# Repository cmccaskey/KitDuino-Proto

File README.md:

# About #
Thunkit Electronics sells electronic kits and rocket altimeters, available at [thunkitelectronics.com](https://thunkitelectronics.com) and [Tindie](https://www.tindie.com/stores/cmccaskey). All designs are open source with schematics, board layouts, code, and BOMs available. The Creative Commons Attribution-NonCommercial-ShareAlike 4.0 International License is used and can be read [here]( https://creativecommons.org/licenses/by-nc-sa/4.0/legalcode).

## Description ###
 <br />
The KitDuino Proto is a 32u4 Arduino compatible with built in prototyping area. The board supports 3 voltage modes selectable by jumpers: 3.3V regulated, 5V regulated, and Vin direct with no regulation.

## Why KitDuino Proto? ## 
The KitDuino Proto is a one of a kind Arduino compatible board. It uses the Atmel ATmega32u4 and can be programmed by the Arduino IDE using the Thunkit Arduino Core available [here](https://github.com/cmccaskey/Thunkit-Arduino-Core/tree/master).The KitDuino Proto has a small prototyping area making it a great addition to your next project.

## Technical Specifications ##
The KitDuino Proto runs at 8MHz to allow for 3.3V and 5V operation. The KitDuino Proto supports 3 voltage modes. By default, the board will run at 3.3V. By installing the jumper in the '5V SEL' position, the board will run at 5V. When powered over USB, due to losses in the regulator circuit, the board will run at approximately 3.8V. If an external voltage sorce of 7V or higher is used, a stable 5V rail will be generated by the regulator. For projects that are always powered off of USB and never see a Vin of more than 5V, the 'Vin SEL' jumper can be installed. This jumper directly connects the USB voltage (after schottky diode) to VCC. Beware! Installing the 'Vin SEL' jumper and connecting a Vin of more than 5V can cause permanent damage to your board!

## BOM ##
KiCad interactive BOM available at [thunkitelectronics.com](https://thunkitelectronics.com).

## Schematic ##
 <br />

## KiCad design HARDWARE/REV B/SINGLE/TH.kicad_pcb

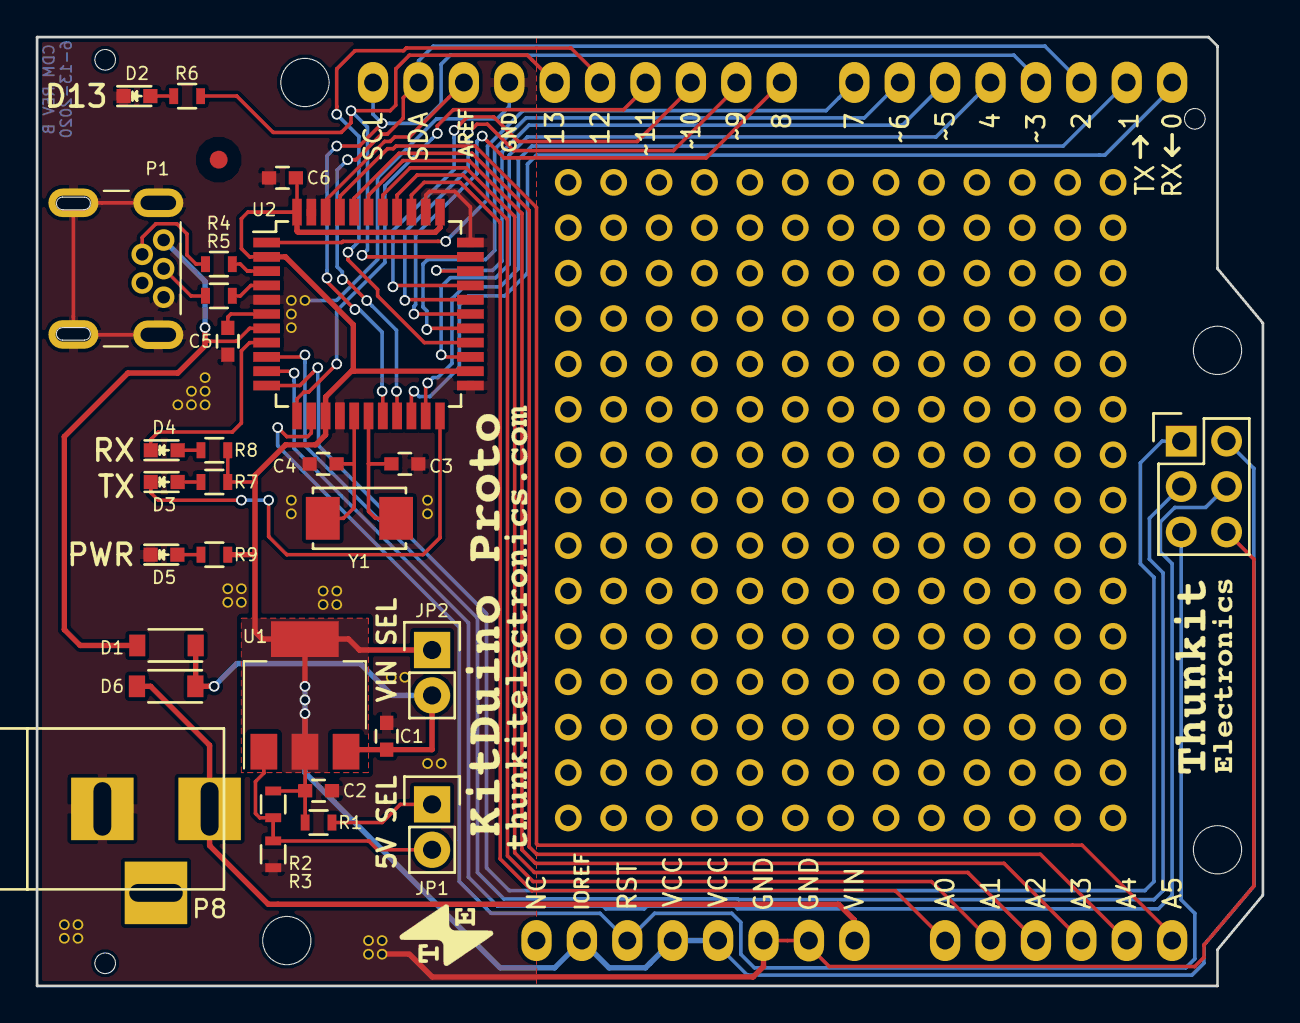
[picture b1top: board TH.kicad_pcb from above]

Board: 2 copper layers, 68.6 x 53.1 mm, 33 parts (0 on the bottom side), 45 nets.

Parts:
C1, C2, C5, C6: 1uF; C_0603
C3, C4: 22pF; C_0603
D1, D6: B5819W; SOD-123
D2: RED; LED_0603
D3, D4: YLW; LED_0603
D5: GRN; LED_0603
JP1, JP2: Jumper_NO_Small; Pin_Header_Straight_1x02
P1: USB MINI B; USB_MINI_B_TH
P2: ICSP; Pin_Header_Straight_2x03
P3, P7: CONN_01X08; Pin_Header_Straight_1x08_Pitch2.54mm_No_Silk_Long_Pads
P4: CONN_01X06; Pin_Header_Straight_1x06_Pitch2.54mm_No_Silk_Long_Pads
P6: CONN_01X10; Pin_Header_Straight_1x10_Pitch2.54mm_No_Silk_Long_Pads
P8: Barrel_Jack_Switch; BARREL_JACK
R1: 732; R_0603
R2: 619; R_0603
R3, R6, R7, R8, R9: 1K; R_0603
R4, R5: 22R; R_0603
U1: AMS1117-ADJ; SOT-223
U2: ATMEGA32U4-M; TQFP-44_10x10mm_Pitch0.8mm
Y1: 8MHz; ABM3

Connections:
AREF: P6.3, U2.42
D+: R5.1, U2.4
D-: R4.1, U2.3
GND: C1.2, C2.2, C3.1, C4.1, C5.2, C6.2, D2.1, D5.1, P1.5, P1.6, P2.6, P3.2, P3.3, P6.4, P8.2, R3.2, U2.5, U2.15, U2.23, U2.33, U2.35, U2.43
MISO: P2.1, U2.11
MOSI: P2.4, U2.10
unnamed: C1.1, D1.1, D6.1, JP2.2, U1.3
unnamed: C3.2, U2.17, Y1.1
unnamed: C4.2, U2.16, Y1.2
unnamed: C5.1, U2.6
unnamed: D2.2, R6.2
unnamed: D3.2, R7.2
unnamed: D4.2, R8.2
unnamed: D5.2, R9.2
unnamed: JP1.1, R1.2
unnamed: JP1.2, R2.2, R3.1, U1.1
unnamed: P1.2, R4.2
unnamed: P1.3, R5.2
PB4: P6.10, U2.28
PB5: P6.9, U2.29
PB6: P6.8, U2.30
PB7: P6.7, U2.12
PC6: P7.6, U2.31
PC7: P6.5, R6.1, U2.32
PD0: P6.1, P7.4, U2.18
PD1: P6.2, P7.3, U2.19
PD2: P7.1, U2.20
PD3: P7.2, U2.21
PD4: P7.5, U2.25
PD6: P6.6, U2.26
PD7: P7.7, U2.27
PE6: P7.8, U2.1
PF0: P4.1, U2.41
PF1: P4.2, U2.40
PF4: P4.3, U2.39
PF5: P4.4, U2.38
PF6: P4.5, U2.37
PF7: P4.6, U2.36
RST: P2.5, P3.6, U2.13
RX_LED: D4.1, U2.8
SCK: P2.3, U2.9
TX_LED: D3.1, U2.22
VBUS: D1.2, P1.1, U2.7
VCC: C2.1, C6.1, JP2.1, P2.2, P3.4, P3.5, P3.7, R1.1, R2.1, R7.1, R8.1, R9.1, U1.2, U1.4, U2.2, U2.14, U2.24, U2.34, U2.44
VIN: D6.2, P3.1, P8.1

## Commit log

2020-07-12 init
2020-07-12 gitignore
2020-07-12 readme
2020-07-25 updated license, added BOM, KiCad 5
2020-07-25 png schematic
2020-07-25 typo
2020-07-25 remove gitignore
2020-07-25 add gitignore
